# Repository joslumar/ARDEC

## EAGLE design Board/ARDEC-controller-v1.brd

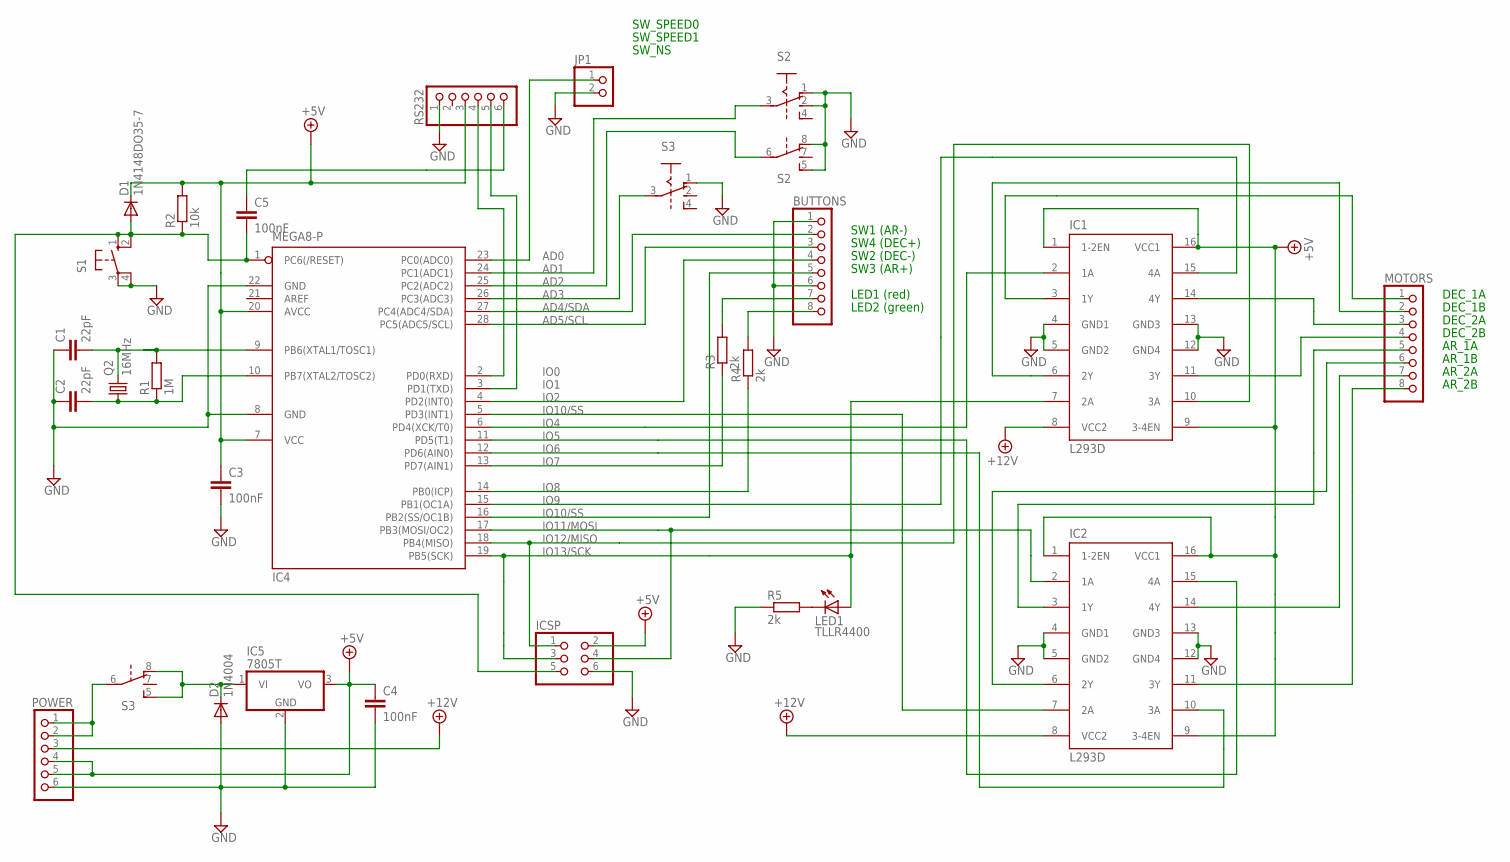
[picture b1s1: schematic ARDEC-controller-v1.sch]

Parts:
BUTTONS: PINHD-1X8; 1X08
C1, C2: 22pF; C2.5-2
C3, C4, C5: 100nF; C025_050-025X075
D1: 1N4148DO35-7; DO35-7
D2: 1N4004; DO41-10
IC1, IC2: L293D; DIL16
IC4: MEGA8-P; DIL28-3
IC5: 7805T; TO220H
ICSP: PINHD-2X3; 2X03
JP1: PINHD-1X2; 1X02
LED1: TLLR4400; LED3MM
MOTORS: PINHD-1X8; 1X08
POWER: PINHD-1X6; 1X06
Q2: 16MHz; HC18U-H
R1: 1M; 0207/10
R2: 10k; 0207/10
R3, R4, R5: 2k; 0207/10
RS232: PINHD-1X6; 1X06
S1: 10-XX; B3F-10XX
S2, S3: SL2C3P

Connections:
+5V: C3.1, C4.1, D1.C, IC1.1 (1-2EN), IC1.9 (3-4EN), IC1.16 (VCC1), IC2.1 (1-2EN), IC2.9 (3-4EN), IC2.16 (VCC1), IC4.7 (VCC), IC4.20 (AVCC), IC5.3 (VO), ICSP.2, POWER.4, POWER.5, R2.2, RS232.3
+12V: IC1.8 (VCC2), IC2.8 (VCC2), POWER.3
AD0: IC4.23 (PC0(ADC0)), JP1.1
AD1: IC4.24 (PC1(ADC1)), S2.3 (Q)
AD2: IC4.25 (PC2(ADC2)), S2.6 (Q)
AD3: IC4.26 (PC3(ADC3)), S3.3 (Q)
AD4/SDA: BUTTONS.2, IC4.27 (PC4(ADC4/SDA))
AD5/SCL: BUTTONS.3, IC4.28 (PC5(ADC5/SCL))
GND: BUTTONS.1, BUTTONS.6, C1.1, C2.1, C3.2, C4.2, D2.A, IC1.4 (GND1), IC1.5 (GND2), IC1.12 (GND4), IC1.13 (GND3), IC2.4 (GND1), IC2.5 (GND2), IC2.12 (GND4), IC2.13 (GND3), IC4.8 (GND), IC4.22 (GND), IC5.2 (GND), ICSP.6, JP1.2, POWER.6, R5.1, RS232.1, S1.3, S1.4 (P1), S2.1 (O), S2.2, S2.5 (R), S2.8 (O), S3.1 (O)
IO0: IC4.2 (PD0(RXD)), RS232.4
IO1: IC4.3 (PD1(TXD)), RS232.5
IO2: BUTTONS.4, IC4.4 (PD2(INT0))
IO4: IC1.2 (1A), IC4.6 (PD4(XCK/T0))
IO5: IC2.15 (4A), IC4.11 (PD5(T1))
IO6: IC2.10 (3A), IC4.12 (PD6(AIN0))
IO7: IC4.13 (PD7(AIN1)), R3.1
IO8: IC4.14 (PB0(ICP)), R4.1
IO9: IC1.15 (4A), IC4.15 (PB1(OC1A))
IO10/SS: BUTTONS.5, IC4.16 (PB2(SS/OC1B))
IO11/MOSI: IC2.2 (1A), IC4.17 (PB3(MOSI/OC2)), ICSP.4
IO12/MISO: IC1.10 (3A), IC4.18 (PB4(MISO)), ICSP.1
IO13/SCK: IC1.7 (2A), IC4.19 (PB5(SCK)), ICSP.3, LED1.A
unnamed: IC1.3 (1Y), MOTORS.1
unnamed: IC1.6 (2Y), MOTORS.2
unnamed: IC1.14 (4Y), MOTORS.3
unnamed: IC1.11 (3Y), MOTORS.4
unnamed: IC2.3 (1Y), MOTORS.5
unnamed: IC2.6 (2Y), MOTORS.6
unnamed: IC2.14 (4Y), MOTORS.7
unnamed: IC2.11 (3Y), MOTORS.8
unnamed: BUTTONS.8, R4.2
unnamed: BUTTONS.7, R3.2
unnamed: POWER.1, POWER.2, S3.6 (Q)
unnamed: LED1.K (C), R5.2
unnamed: C1.2, IC4.9 (PB6(XTAL1/TOSC1)), Q2.2, R1.2
unnamed: C2.2, IC4.10 (PB7(XTAL2/TOSC2)), Q2.1, R1.1
unnamed: IC2.7 (2A), IC4.5 (PD3(INT1))
unnamed: C5.1, RS232.6
unnamed: D2.C, IC5.1 (VI), S3.5 (R), S3.8 (O)
RESET: C5.2, D1.A, IC4.1 (PC6(/RESET)), ICSP.5, R2.1, S1.1 (S), S1.2 (S1)

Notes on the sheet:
DEC_1A
DEC_1B
DEC_2A
DEC_2B
AR_1A
AR_1B
AR_2A
AR_2B
SW1 (AR-)
SW4 (DEC+)
SW2 (DEC-)
SW3 (AR+)
LED1 (red)
LED2 (green)
SW_NS
SW_SPEED1
SW_SPEED0

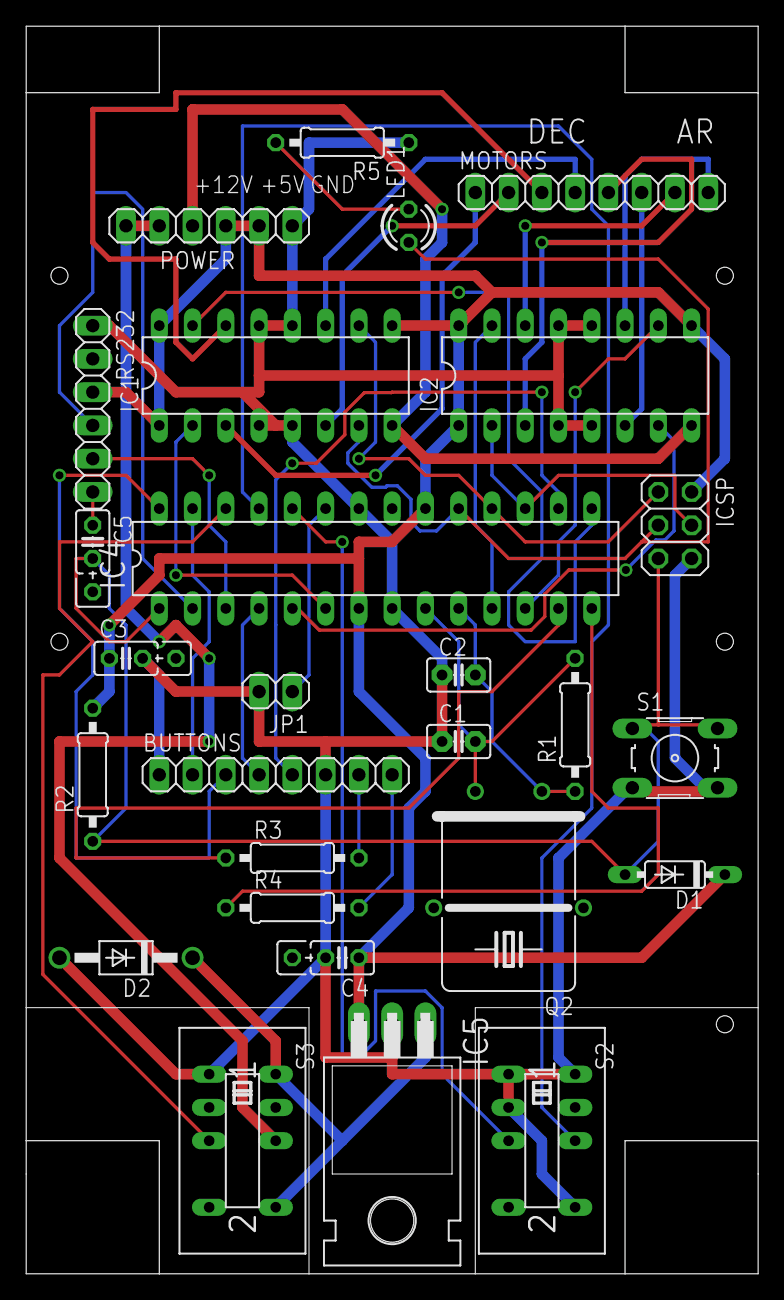
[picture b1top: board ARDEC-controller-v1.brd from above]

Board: 2 copper layers, 55.9 x 95.2 mm, 27 parts (0 on the bottom side), 40 nets.

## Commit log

2017-05-20 First
2017-05-20 deleted: ARDECv1_1.ino.~1~ deleted: ARDECv1_1.ino.~2~ deleted: ARDECv1_1.ino.~5~ deleted: ARDECv1_1.ino.~6~
2017-05-20 new file: Board/ARDEC-controller-v1.brd new file: Board/ARDEC-controller-v1.sch
2017-05-20 renamed: ARDECv1_1.ino -> ARDEC.ino
2019-11-10 Version 2.0
2019-11-16 Realtime correction
2019-11-17 Minor updates
2019-11-17 Update startup version line with CLK_ADJ
